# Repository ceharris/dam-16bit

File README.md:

dam-16bit
=========

This repository contains KiCad sources for 16-bit digital acquisition
module suitable for use as passive bus monitor. It is designed to be
compatible with the [icm7212m-display](https://github.com/ceharris/icm7212m-display). Using this module and the complementary display module, a 16-bit 
input can be continuously displayed in hexadecimal notation on the 
4-digit LED display.

This module uses a NE555 timer in astable mode to produce a 1 kHz 
clock. At each clock pulse a 2-bit counter is incremented. The counter
outputs are used as address lines for one unit of a 74HC139 dual 2-to-4
decoder circuit. The active low chip select outputs of the decoder are
connected to the chip select inputs of two 74HC244 octal buffers. The
74HC244 consists of two 4-bit buffer units which can be independently 
selected. The outputs of the 4-bit buffer units on each of the 74HC244
circuits are connected to the B0..3 outputs for the display module.

The 2-bit counter outputs are also used to provide the DS1 and DS2 
(digit select) inputs for the display module.

With this design, the sample rate for the 16-bit inputs is approximately
250 Hz. With each clock pulse, four bits of the input are sampled and
the result is sent to the corresponding display digit.

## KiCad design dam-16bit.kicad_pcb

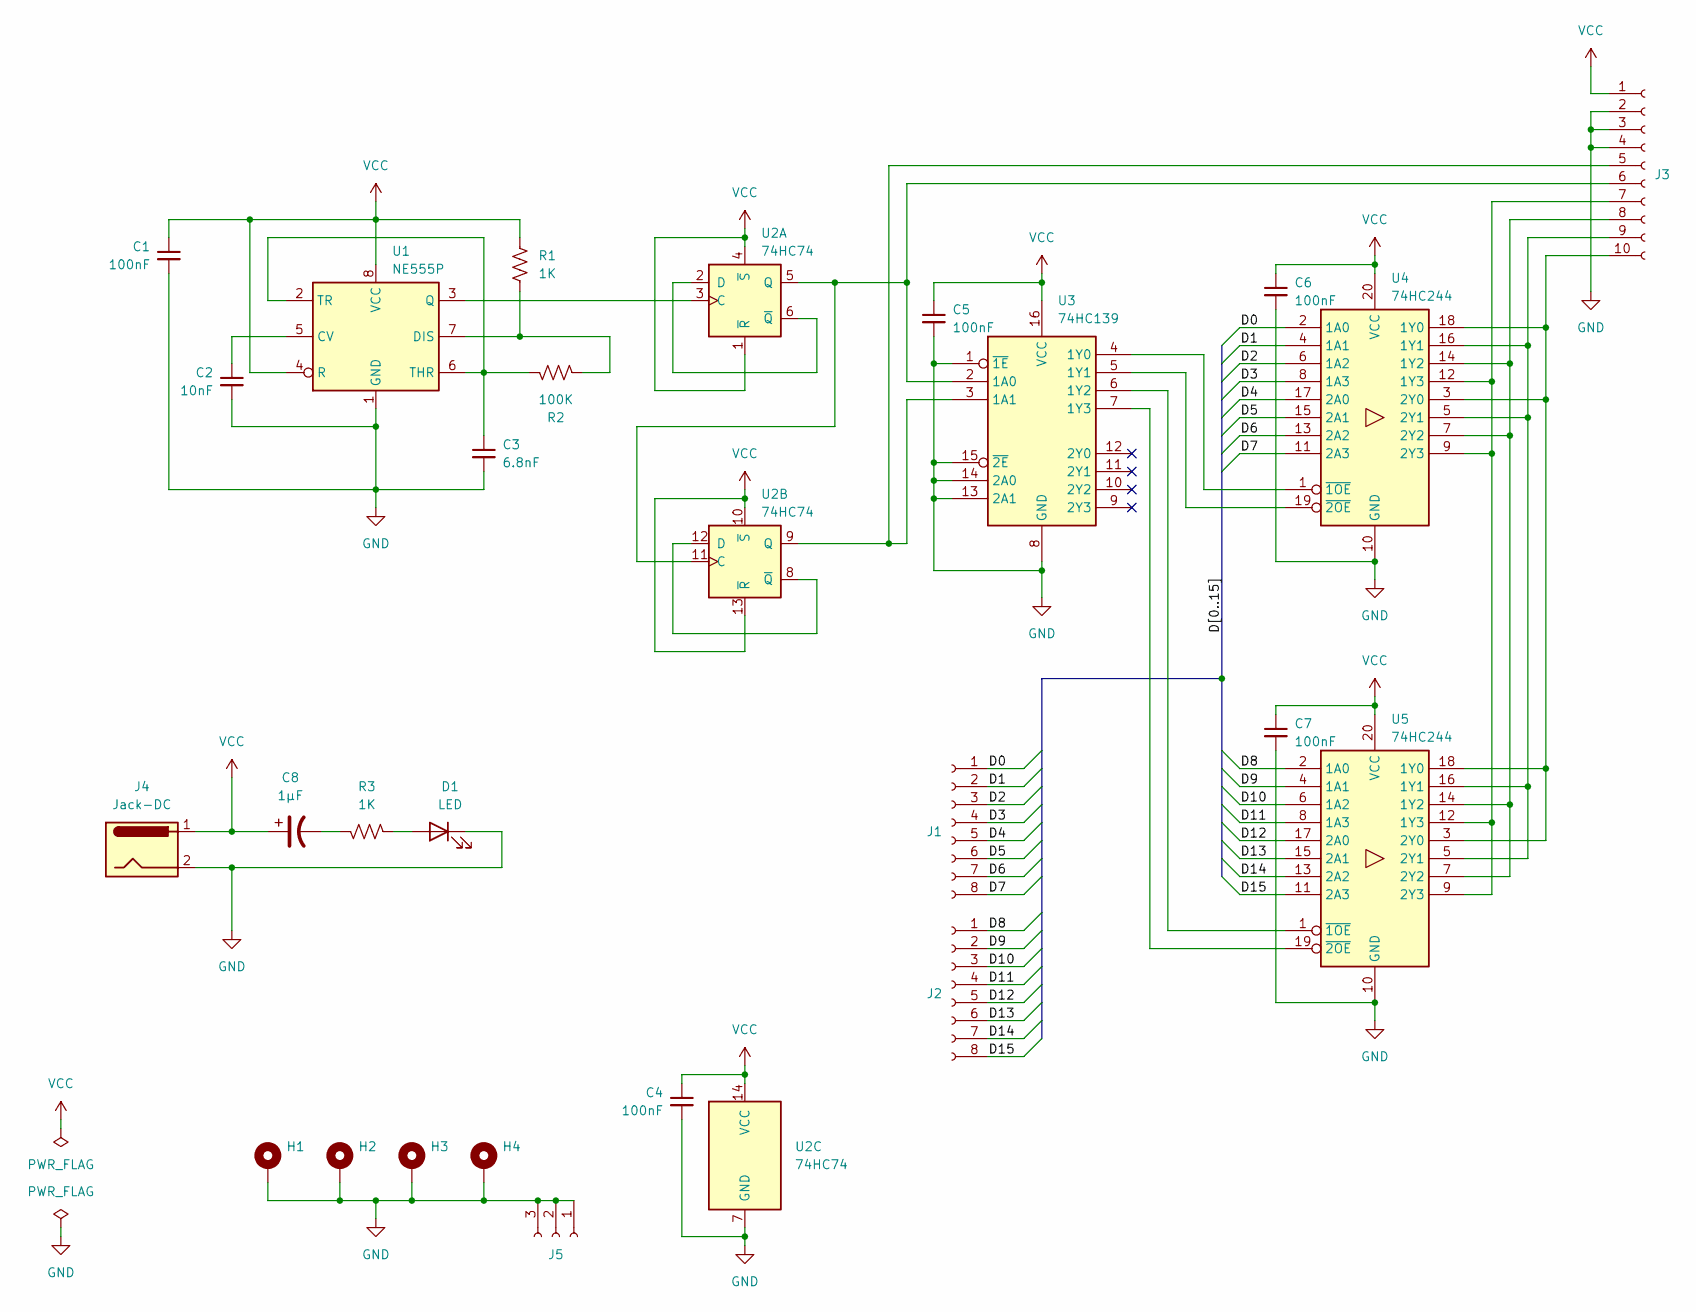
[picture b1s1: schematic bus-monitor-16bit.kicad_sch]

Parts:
C1, C4, C5, C6, C7: 100nF; C_Disc_D3.0mm_W1.6mm_P2.50mm
C2: 10nF; C_Disc_D3.0mm_W1.6mm_P2.50mm
C3: 6.8nF; C_Disc_D4.3mm_W1.9mm_P5.00mm
C8: 1µF; CP_Radial_D5.0mm_P2.00mm
D1: LED; LED_D3.0mm
H1, H2, H3, H4: MountingHole_Pad; MountingHole_2.2mm_M2_DIN965_Pad
J1, J2: Conn_01x08_Socket; PinSocket_1x08_P2.54mm_Vertical
J3: Conn_01x10_Socket; PinSocket_1x10_P2.54mm_Vertical
J4: Jack-DC; BarrelJack_CUI_PJ-063AH_Horizontal
J5: Conn_01x03_Socket; PinSocket_1x03_P2.54mm_Vertical
R1, R3: 1K; R_Axial_DIN0207_L6.3mm_D2.5mm_P7.62mm_Horizontal
R2: 100K; R_Axial_DIN0207_L6.3mm_D2.5mm_P7.62mm_Horizontal
U1: NE555P; DIP-8_W7.62mm_Socket
U2: 74HC74; DIP-14_W7.62mm_Socket
U3: 74HC139; DIP-16_W7.62mm_Socket
U4, U5: 74HC244; DIP-20_W7.62mm_Socket

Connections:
/D0: J1.1, U4.2 (1A0)
/D1: J1.2, U4.4 (1A1)
/D2: J1.3, U4.6 (1A2)
/D3: J1.4, U4.8 (1A3)
/D4: J1.5, U4.17 (2A0)
/D5: J1.6, U4.15 (2A1)
/D6: J1.7, U4.13 (2A2)
/D7: J1.8, U4.11 (2A3)
/D8: J2.1, U5.2 (1A0)
/D9: J2.2, U5.4 (1A1)
/D10: J2.3, U5.6 (1A2)
/D11: J2.4, U5.8 (1A3)
/D12: J2.5, U5.17 (2A0)
/D13: J2.6, U5.15 (2A1)
/D14: J2.7, U5.13 (2A2)
/D15: J2.8, U5.11 (2A3)
GND: C1.2, C2.2, C3.2, C4.2, C5.2, C6.2, C7.2, D1.1 (K), H1.1, H2.1, H3.1, H4.1, J3.2, J3.3, J3.4, J4.2, J5.1, J5.2, J5.3, U1.1 (GND), U2.7 (GND), U3.1 (~1E), U3.8 (GND), U3.13 (2A1), U3.14 (2A0), U3.15 (~2E), U4.10 (GND), U5.10 (GND)
unnamed: C8.2, R3.2
unnamed: D1.2 (A), R3.1
unnamed: J3.5, U2.9 (Q), U3.3 (1A1)
unnamed: J3.6, U2.5 (Q), U2.11 (C), U3.2 (1A0)
unnamed: J3.7, U4.9 (2Y3), U4.12 (1Y3), U5.9 (2Y3), U5.12 (1Y3)
unnamed: J3.8, U4.7 (2Y2), U4.14 (1Y2), U5.7 (2Y2), U5.14 (1Y2)
unnamed: J3.9, U4.5 (2Y1), U4.16 (1Y1), U5.5 (2Y1), U5.16 (1Y1)
unnamed: J3.10, U4.3 (2Y0), U4.18 (1Y0), U5.3 (2Y0), U5.18 (1Y0)
unnamed: C2.1, U1.5 (CV)
unnamed: R1.2, R2.2, U1.7 (DIS)
unnamed: U1.3 (Q), U2.3 (C)
unnamed: C3.1, R2.1, U1.2 (TR), U1.6 (THR)
unnamed: U2.2 (D), U2.6 (~Q)
unnamed: U2.8 (~Q), U2.12 (D)
unnamed: U3.4 (1Y0), U4.1 (~1OE)
unnamed: U3.5 (1Y1), U4.19 (~2OE)
unnamed: U3.6 (1Y2), U5.1 (~1OE)
unnamed: U3.7 (1Y3), U5.19 (~2OE)
VCC: C1.1, C4.1, C5.1, C6.1, C7.1, C8.1, J3.1, J4.1, R1.1, U1.4 (R), U1.8 (VCC), U2.1 (~R), U2.4 (~S), U2.10 (~S), U2.13 (~R), U2.14 (VCC), U3.16 (VCC), U4.20 (VCC), U5.20 (VCC)

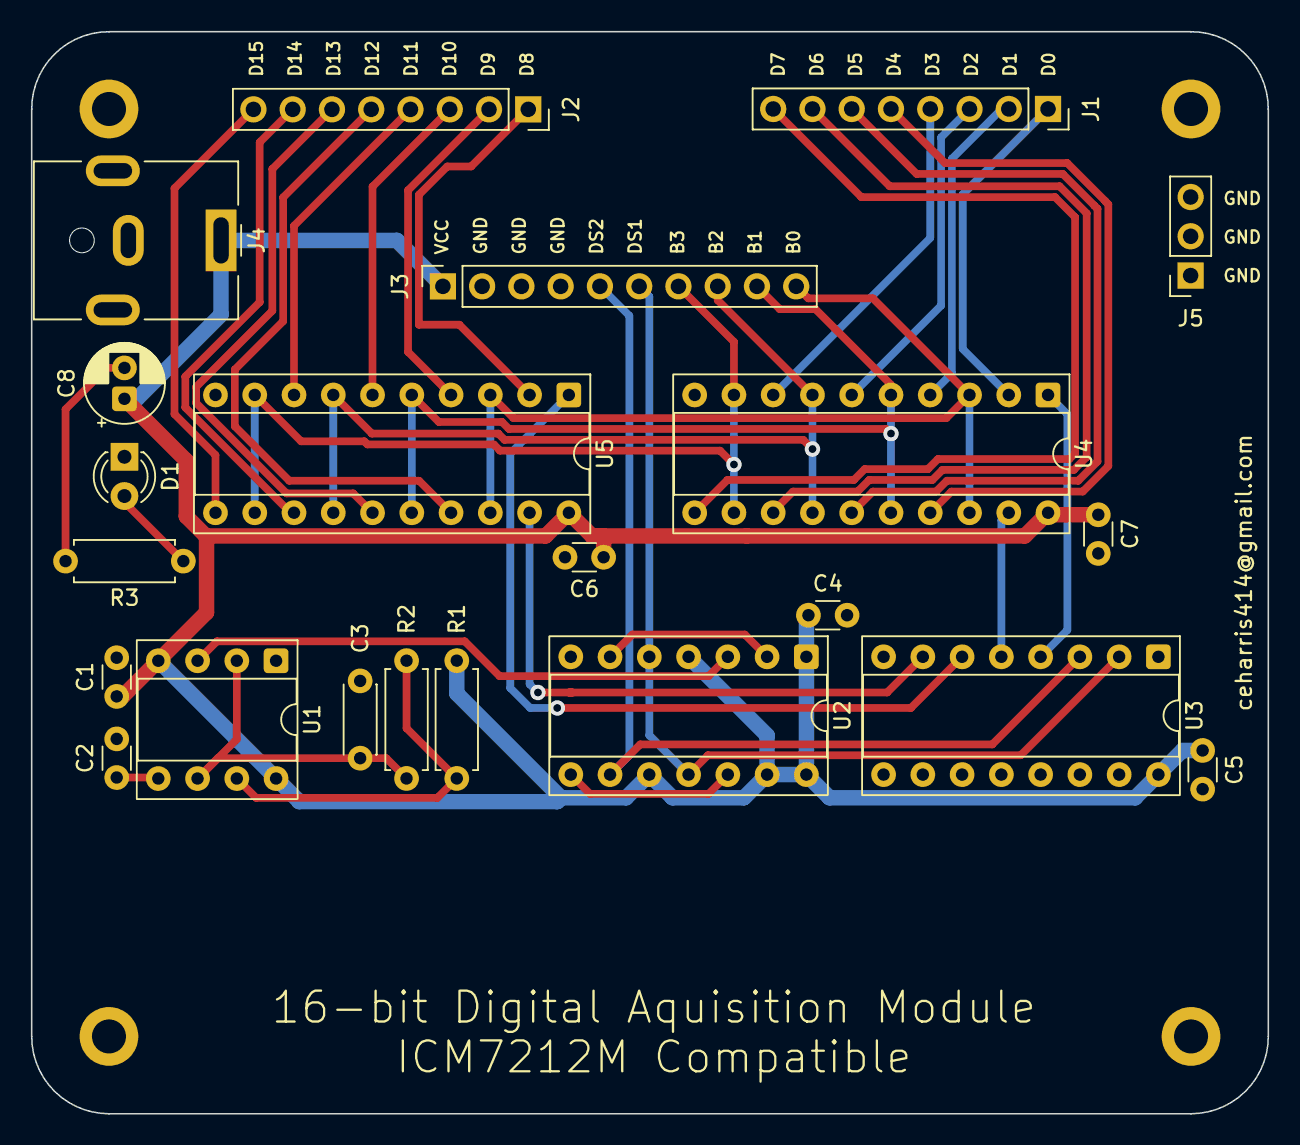
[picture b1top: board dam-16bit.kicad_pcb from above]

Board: 2 copper layers, 80.0 x 70.0 mm, 26 parts (0 on the bottom side), 36 nets.

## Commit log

2025-06-19 rename for consistency
2025-06-19 minor clarification
